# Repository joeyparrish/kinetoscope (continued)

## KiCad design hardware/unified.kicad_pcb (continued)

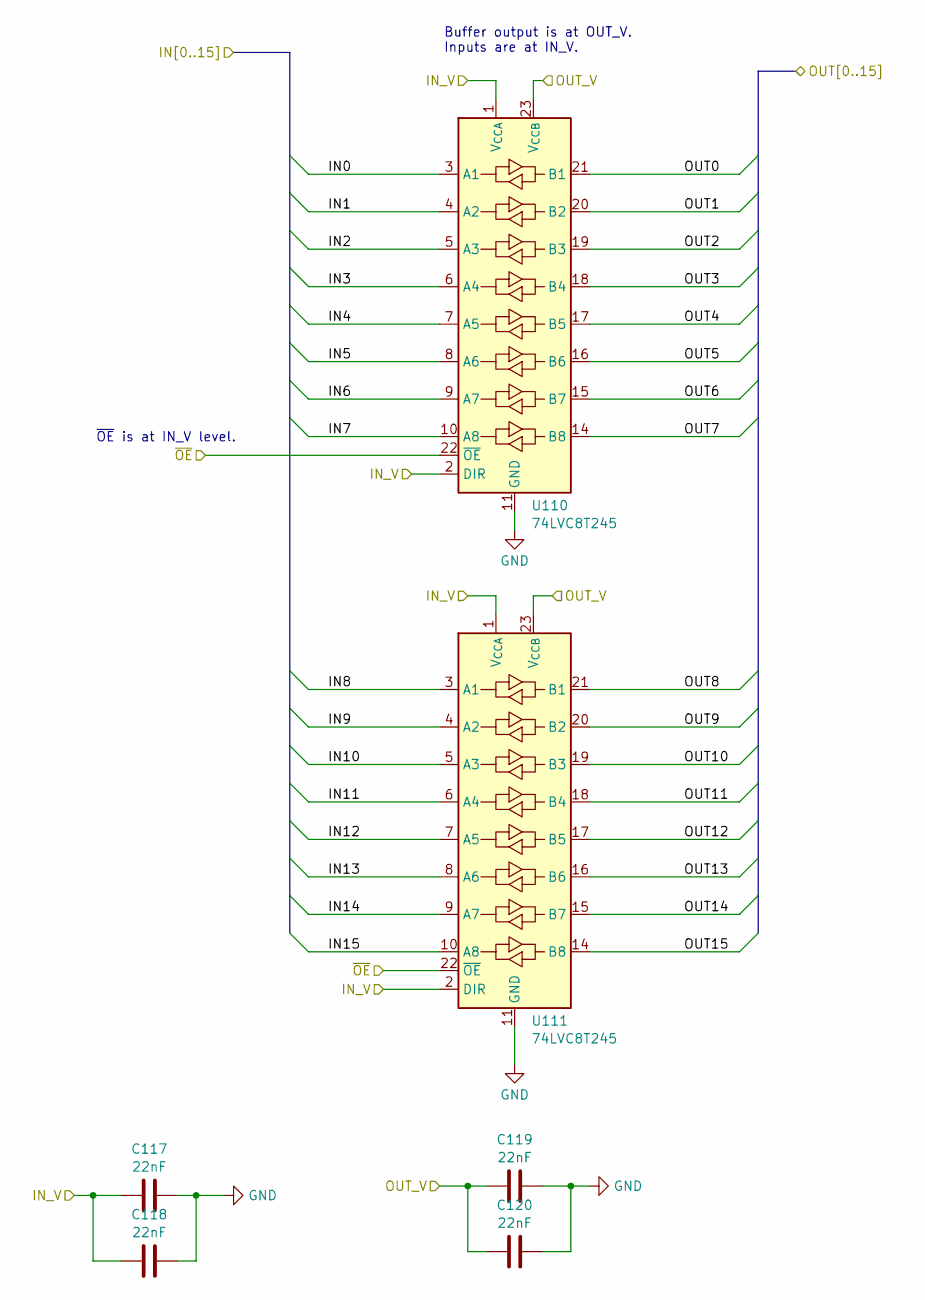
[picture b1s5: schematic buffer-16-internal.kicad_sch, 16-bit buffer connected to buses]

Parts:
C117, C118, C119, C120: 22nF; C_0603_1608Metric; Mouser Part Number 80-C0603C223K4R; JLCPCB Part Number CL10B223KB8NNNC
U110, U111: 74LVC8T245; TSSOP-24_4.4x7.8mm_P0.65mm; Mouser Part Number 595-SN74LVC8T245PWR; JLCPCB Part Number C27643

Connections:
+3.3V: C117.1, C118.1, C119.1, C120.1, U110.1 (V_{CCA}), U110.2 (DIR), U110.23 (V_{CCB}), U110.24 (V_{CCB}), U111.1 (V_{CCA}), U111.2 (DIR), U111.23 (V_{CCB}), U111.24 (V_{CCB}); also elsewhere on the board
/sram-bank-internal/SRAM_DATA0: U110.21 (B1); also elsewhere on the board
/sram-bank-internal/SRAM_DATA1: U110.20 (B2); also elsewhere on the board
/sram-bank-internal/SRAM_DATA2: U110.19 (B3); also elsewhere on the board
/sram-bank-internal/SRAM_DATA3: U110.18 (B4); also elsewhere on the board
/sram-bank-internal/SRAM_DATA4: U110.17 (B5); also elsewhere on the board
/sram-bank-internal/SRAM_DATA5: U110.16 (B6); also elsewhere on the board
/sram-bank-internal/SRAM_DATA6: U110.15 (B7); also elsewhere on the board
/sram-bank-internal/SRAM_DATA7: U110.14 (B8); also elsewhere on the board
/sram-bank-internal/SRAM_DATA8: U111.21 (B1); also elsewhere on the board
/sram-bank-internal/SRAM_DATA9: U111.20 (B2); also elsewhere on the board
/sram-bank-internal/SRAM_DATA10: U111.19 (B3); also elsewhere on the board
/sram-bank-internal/SRAM_DATA11: U111.18 (B4); also elsewhere on the board
/sram-bank-internal/SRAM_DATA12: U111.17 (B5); also elsewhere on the board
/sram-bank-internal/SRAM_DATA13: U111.16 (B6); also elsewhere on the board
/sram-bank-internal/SRAM_DATA14: U111.15 (B7); also elsewhere on the board
/sram-bank-internal/SRAM_DATA15: U111.14 (B8); also elsewhere on the board
/sram-bank-internal/~UC_CONTROL: U110.22 (~OE), U111.22 (~OE); also elsewhere on the board
GND: C117.2, C118.2, C119.2, C120.2, U110.11 (GND), U110.12 (GND), U110.13 (GND), U111.11 (GND), U111.12 (GND), U111.13 (GND); also elsewhere on the board
SRAM_D_IN0: U110.3 (A1); also elsewhere on the board
SRAM_D_IN1: U110.4 (A2); also elsewhere on the board
SRAM_D_IN2: U110.5 (A3); also elsewhere on the board
SRAM_D_IN3: U110.6 (A4); also elsewhere on the board
SRAM_D_IN4: U110.7 (A5); also elsewhere on the board
SRAM_D_IN5: U110.8 (A6); also elsewhere on the board
SRAM_D_IN6: U110.9 (A7); also elsewhere on the board
SRAM_D_IN7: U110.10 (A8); also elsewhere on the board
SRAM_D_IN8: U111.3 (A1); also elsewhere on the board
SRAM_D_IN9: U111.4 (A2); also elsewhere on the board
SRAM_D_IN10: U111.5 (A3); also elsewhere on the board
SRAM_D_IN11: U111.6 (A4); also elsewhere on the board
SRAM_D_IN12: U111.7 (A5); also elsewhere on the board
SRAM_D_IN13: U111.8 (A6); also elsewhere on the board
SRAM_D_IN14: U111.9 (A7); also elsewhere on the board
SRAM_D_IN15: U111.10 (A8); also elsewhere on the board

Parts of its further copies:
C121, C122, C123, C124, C204, C205, C206, C207, C208, C209, C210, C211: 22nF; C_0603_1608Metric; Mouser Part Number 80-C0603C223K4R; JLCPCB Part Number CL10B223KB8NNNC
U112, U113, U203, U204, U205, U206: 74LVC8T245; TSSOP-24_4.4x7.8mm_P0.65mm; Mouser Part Number 595-SN74LVC8T245PWR; JLCPCB Part Number C27643

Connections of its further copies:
+3.3V: C121.1, C122.1, C204.1, C205.1, C208.1, C209.1, C210.1, C211.1, U112.1 (V_{CCA}), U112.2 (DIR), U113.1 (V_{CCA}), U113.2 (DIR), U203.1 (V_{CCA}), U203.2 (DIR), U204.1 (V_{CCA}), U204.2 (DIR), U205.1 (V_{CCA}), U205.2 (DIR), U205.23 (V_{CCB}), U205.24 (V_{CCB}), U206.1 (V_{CCA}), U206.2 (DIR), U206.23 (V_{CCB}), U206.24 (V_{CCB}); also elsewhere on the board
+5V: C123.1, C124.1, C206.1, C207.1, U112.23 (V_{CCB}), U112.24 (V_{CCB}), U113.23 (V_{CCB}), U113.24 (V_{CCB}), U203.23 (V_{CCB}), U203.24 (V_{CCB}), U204.23 (V_{CCB}), U204.24 (V_{CCB}); also elsewhere on the board
/sram-bank-internal1/SRAM_DATA0: U203.3 (A1), U205.21 (B1); also elsewhere on the board
/sram-bank-internal1/SRAM_DATA1: U203.4 (A2), U205.20 (B2); also elsewhere on the board
/sram-bank-internal1/SRAM_DATA2: U203.5 (A3), U205.19 (B3); also elsewhere on the board
/sram-bank-internal1/SRAM_DATA3: U203.6 (A4), U205.18 (B4); also elsewhere on the board
/sram-bank-internal1/SRAM_DATA4: U203.7 (A5), U205.17 (B5); also elsewhere on the board
/sram-bank-internal1/SRAM_DATA5: U203.8 (A6), U205.16 (B6); also elsewhere on the board
/sram-bank-internal1/SRAM_DATA6: U203.9 (A7), U205.15 (B7); also elsewhere on the board
/sram-bank-internal1/SRAM_DATA7: U203.10 (A8), U205.14 (B8); also elsewhere on the board
/sram-bank-internal1/SRAM_DATA8: U204.3 (A1), U206.21 (B1); also elsewhere on the board
/sram-bank-internal1/SRAM_DATA9: U204.4 (A2), U206.20 (B2); also elsewhere on the board
/sram-bank-internal1/SRAM_DATA10: U204.5 (A3), U206.19 (B3); also elsewhere on the board
/sram-bank-internal1/SRAM_DATA11: U204.6 (A4), U206.18 (B4); also elsewhere on the board
/sram-bank-internal1/SRAM_DATA12: U204.7 (A5), U206.17 (B5); also elsewhere on the board
/sram-bank-internal1/SRAM_DATA13: U204.8 (A6), U206.16 (B6); also elsewhere on the board
/sram-bank-internal1/SRAM_DATA14: U204.9 (A7), U206.15 (B7); also elsewhere on the board
/sram-bank-internal1/SRAM_DATA15: U204.10 (A8), U206.14 (B8); also elsewhere on the board
/sram-bank-internal1/~SRAM_FINAL_OE: U203.22 (~OE), U204.22 (~OE); also elsewhere on the board
/sram-bank-internal1/~UC_CONTROL: U205.22 (~OE), U206.22 (~OE); also elsewhere on the board
/sram-bank-internal/SRAM_DATA0: U112.3 (A1); also elsewhere on the board
/sram-bank-internal/SRAM_DATA1: U112.4 (A2); also elsewhere on the board
/sram-bank-internal/SRAM_DATA2: U112.5 (A3); also elsewhere on the board
/sram-bank-internal/SRAM_DATA3: U112.6 (A4); also elsewhere on the board
/sram-bank-internal/SRAM_DATA4: U112.7 (A5); also elsewhere on the board
/sram-bank-internal/SRAM_DATA5: U112.8 (A6); also elsewhere on the board
/sram-bank-internal/SRAM_DATA6: U112.9 (A7); also elsewhere on the board
/sram-bank-internal/SRAM_DATA7: U112.10 (A8); also elsewhere on the board
/sram-bank-internal/SRAM_DATA8: U113.3 (A1); also elsewhere on the board
/sram-bank-internal/SRAM_DATA9: U113.4 (A2); also elsewhere on the board
/sram-bank-internal/SRAM_DATA10: U113.5 (A3); also elsewhere on the board
/sram-bank-internal/SRAM_DATA11: U113.6 (A4); also elsewhere on the board
/sram-bank-internal/SRAM_DATA12: U113.7 (A5); also elsewhere on the board
/sram-bank-internal/SRAM_DATA13: U113.8 (A6); also elsewhere on the board
/sram-bank-internal/SRAM_DATA14: U113.9 (A7); also elsewhere on the board
/sram-bank-internal/SRAM_DATA15: U113.10 (A8); also elsewhere on the board
/sram-bank-internal/~SRAM_FINAL_OE: U112.22 (~OE), U113.22 (~OE); also elsewhere on the board
GND: C121.2, C122.2, C123.2, C124.2, C204.2, C205.2, C206.2, C207.2, C208.2, C209.2, C210.2, C211.2, U112.11 (GND), U112.12 (GND), U112.13 (GND), U113.11 (GND), U113.12 (GND), U113.13 (GND), U203.11 (GND), U203.12 (GND), U203.13 (GND), U204.11 (GND), U204.12 (GND), U204.13 (GND), U205.11 (GND), U205.12 (GND), U205.13 (GND), U206.11 (GND), U206.12 (GND), U206.13 (GND); also elsewhere on the board
SEGA_D0: U112.21 (B1), U203.21 (B1); also elsewhere on the board
SEGA_D1: U112.20 (B2), U203.20 (B2); also elsewhere on the board
SEGA_D2: U112.19 (B3), U203.19 (B3); also elsewhere on the board
SEGA_D3: U112.18 (B4), U203.18 (B4); also elsewhere on the board
SEGA_D4: U112.17 (B5), U203.17 (B5); also elsewhere on the board
SEGA_D5: U112.16 (B6), U203.16 (B6); also elsewhere on the board
SEGA_D6: U112.15 (B7), U203.15 (B7); also elsewhere on the board
SEGA_D7: U112.14 (B8), U203.14 (B8); also elsewhere on the board
SEGA_D8: U113.21 (B1), U204.21 (B1); also elsewhere on the board
SEGA_D9: U113.20 (B2), U204.20 (B2); also elsewhere on the board
SEGA_D10: U113.19 (B3), U204.19 (B3); also elsewhere on the board
SEGA_D11: U113.18 (B4), U204.18 (B4); also elsewhere on the board
SEGA_D12: U113.17 (B5), U204.17 (B5); also elsewhere on the board
SEGA_D13: U113.16 (B6), U204.16 (B6); also elsewhere on the board
SEGA_D14: U113.15 (B7), U204.15 (B7); also elsewhere on the board
SEGA_D15: U113.14 (B8), U204.14 (B8); also elsewhere on the board
SRAM_D_IN0: U205.3 (A1); also elsewhere on the board
SRAM_D_IN1: U205.4 (A2); also elsewhere on the board
SRAM_D_IN2: U205.5 (A3); also elsewhere on the board
SRAM_D_IN3: U205.6 (A4); also elsewhere on the board
SRAM_D_IN4: U205.7 (A5); also elsewhere on the board
SRAM_D_IN5: U205.8 (A6); also elsewhere on the board
SRAM_D_IN6: U205.9 (A7); also elsewhere on the board
SRAM_D_IN7: U205.10 (A8); also elsewhere on the board
SRAM_D_IN8: U206.3 (A1); also elsewhere on the board
SRAM_D_IN9: U206.4 (A2); also elsewhere on the board
SRAM_D_IN10: U206.5 (A3); also elsewhere on the board
SRAM_D_IN11: U206.6 (A4); also elsewhere on the board
SRAM_D_IN12: U206.7 (A5); also elsewhere on the board
SRAM_D_IN13: U206.8 (A6); also elsewhere on the board
SRAM_D_IN14: U206.9 (A7); also elsewhere on the board
SRAM_D_IN15: U206.10 (A8); also elsewhere on the board

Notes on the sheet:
Buffer output is at OUT_V. Inputs are at IN_V.
~{OE} is at IN_V level.

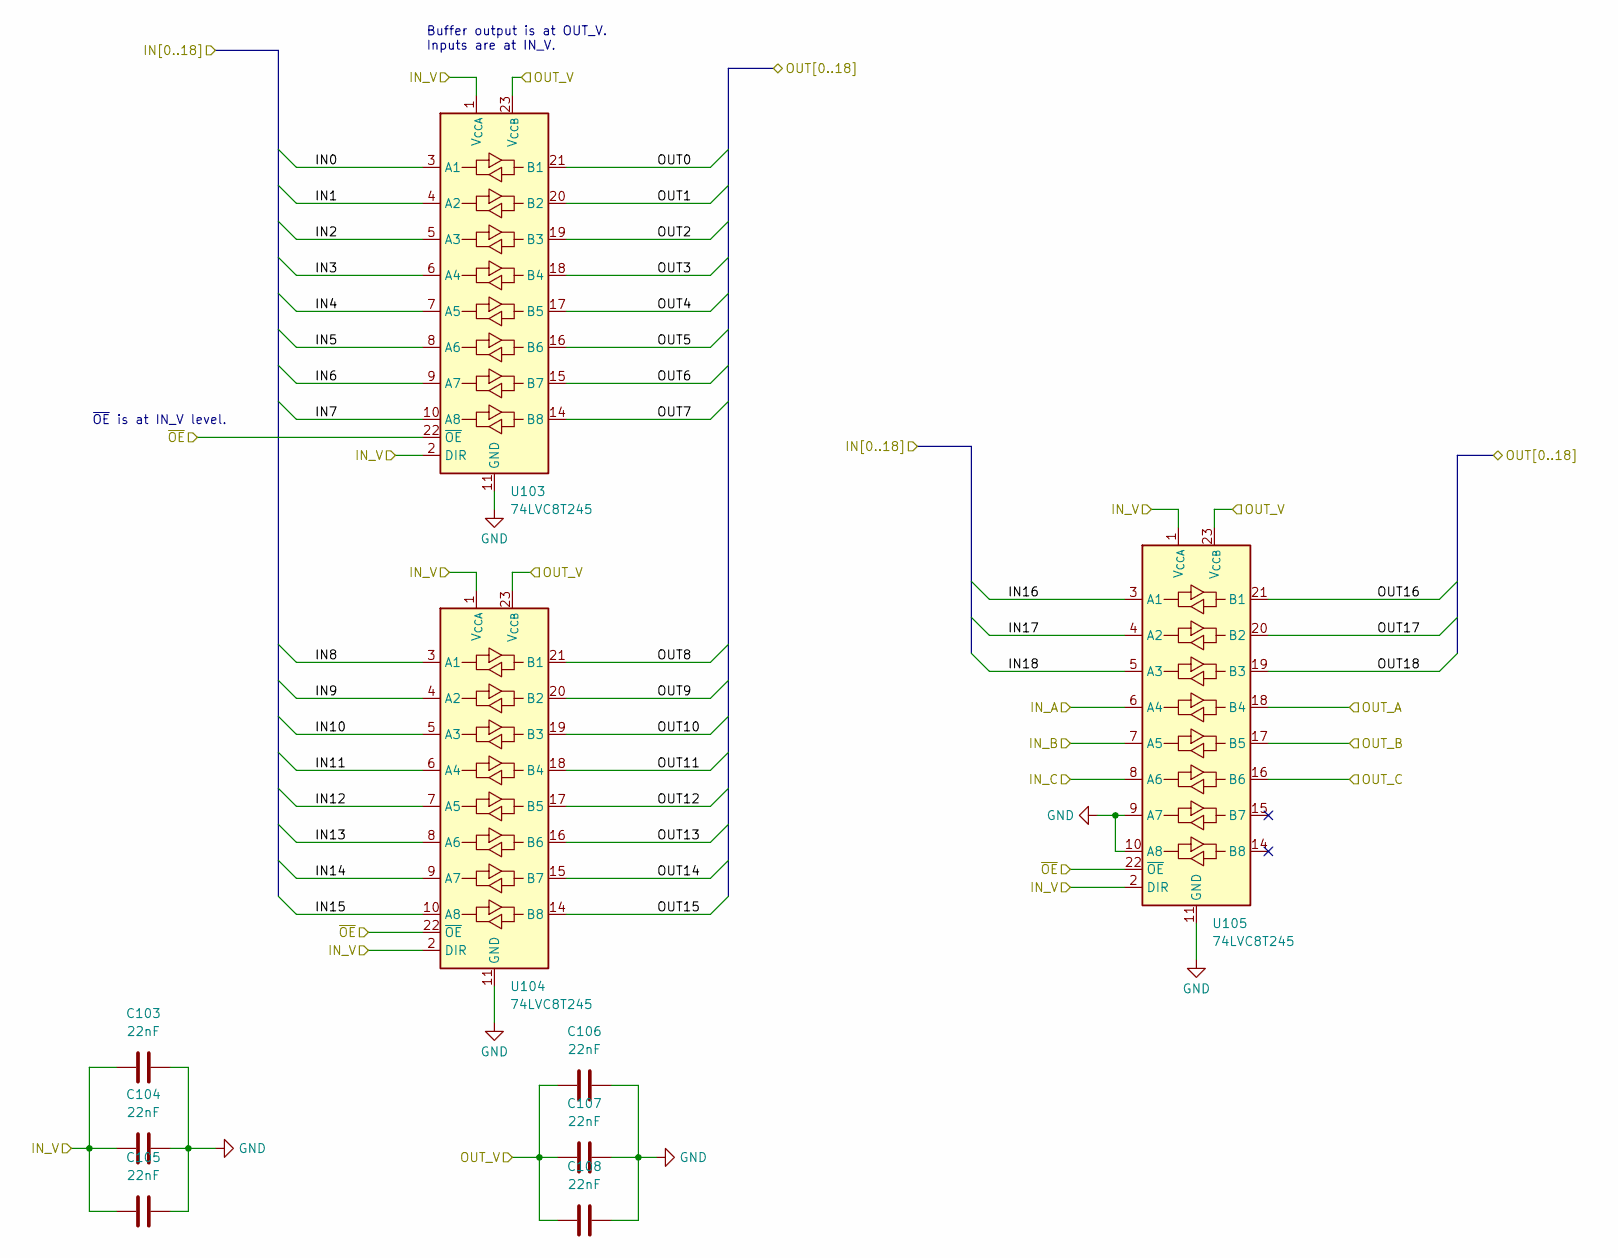
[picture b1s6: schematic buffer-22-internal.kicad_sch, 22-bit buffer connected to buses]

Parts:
C103, C104, C105, C106, C107, C108: 22nF; C_0603_1608Metric; Mouser Part Number 80-C0603C223K4R; JLCPCB Part Number CL10B223KB8NNNC
U103, U104, U105: 74LVC8T245; TSSOP-24_4.4x7.8mm_P0.65mm; Mouser Part Number 595-SN74LVC8T245PWR; JLCPCB Part Number C27643

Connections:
+3.3V: C103.1, C104.1, C105.1, C106.1, C107.1, C108.1, U103.1 (V_{CCA}), U103.2 (DIR), U103.23 (V_{CCB}), U103.24 (V_{CCB}), U104.1 (V_{CCA}), U104.2 (DIR), U104.23 (V_{CCB}), U104.24 (V_{CCB}), U105.1 (V_{CCA}), U105.2 (DIR), U105.8 (A6), U105.23 (V_{CCB}), U105.24 (V_{CCB}); also elsewhere on the board
/sram-bank-internal/SRAM_A0: U103.21 (B1); also elsewhere on the board
/sram-bank-internal/SRAM_A1: U103.20 (B2); also elsewhere on the board
/sram-bank-internal/SRAM_A2: U103.19 (B3); also elsewhere on the board
/sram-bank-internal/SRAM_A3: U103.18 (B4); also elsewhere on the board
/sram-bank-internal/SRAM_A4: U103.17 (B5); also elsewhere on the board
/sram-bank-internal/SRAM_A5: U103.16 (B6); also elsewhere on the board
/sram-bank-internal/SRAM_A6: U103.15 (B7); also elsewhere on the board
/sram-bank-internal/SRAM_A7: U103.14 (B8); also elsewhere on the board
/sram-bank-internal/SRAM_A8: U104.21 (B1); also elsewhere on the board
/sram-bank-internal/SRAM_A9: U104.20 (B2); also elsewhere on the board
/sram-bank-internal/SRAM_A10: U104.19 (B3); also elsewhere on the board
/sram-bank-internal/SRAM_A11: U104.18 (B4); also elsewhere on the board
/sram-bank-internal/SRAM_A12: U104.17 (B5); also elsewhere on the board
/sram-bank-internal/SRAM_A13: U104.16 (B6); also elsewhere on the board
/sram-bank-internal/SRAM_A14: U104.15 (B7); also elsewhere on the board
/sram-bank-internal/SRAM_A15: U104.14 (B8); also elsewhere on the board
/sram-bank-internal/SRAM_A16: U105.21 (B1); also elsewhere on the board
/sram-bank-internal/SRAM_A17: U105.20 (B2); also elsewhere on the board
/sram-bank-internal/SRAM_A18: U105.19 (B3); also elsewhere on the board
/sram-bank-internal/~SEGA_CONTROL: U103.22 (~OE), U104.22 (~OE), U105.22 (~OE); also elsewhere on the board
/sram-bank-internal/~SRAM_FINAL_CE: U105.17 (B5); also elsewhere on the board
/sram-bank-internal/~SRAM_FINAL_OE: U105.18 (B4); also elsewhere on the board
/sram-bank-internal/~SRAM_FINAL_WE: U105.16 (B6); also elsewhere on the board
/sram-bank-internal/~SRAM_OE: U105.6 (A4); also elsewhere on the board
GND: C103.2, C104.2, C105.2, C106.2, C107.2, C108.2, U103.11 (GND), U103.12 (GND), U103.13 (GND), U104.11 (GND), U104.12 (GND), U104.13 (GND), U105.9 (A7), U105.10 (A8), U105.11 (GND), U105.12 (GND), U105.13 (GND); also elsewhere on the board
SEGA_A1: U103.3 (A1); also elsewhere on the board
SEGA_A2: U103.4 (A2); also elsewhere on the board
SEGA_A3: U103.5 (A3); also elsewhere on the board
SEGA_A4: U103.6 (A4); also elsewhere on the board
SEGA_A5: U103.7 (A5); also elsewhere on the board
SEGA_A6: U103.8 (A6); also elsewhere on the board
SEGA_A7: U103.9 (A7); also elsewhere on the board
SEGA_A8: U103.10 (A8); also elsewhere on the board
SEGA_A9: U104.3 (A1); also elsewhere on the board
SEGA_A10: U104.4 (A2); also elsewhere on the board
SEGA_A11: U104.5 (A3); also elsewhere on the board
SEGA_A12: U104.6 (A4); also elsewhere on the board
SEGA_A13: U104.7 (A5); also elsewhere on the board
SEGA_A14: U104.8 (A6); also elsewhere on the board
SEGA_A15: U104.9 (A7); also elsewhere on the board
SEGA_A16: U104.10 (A8); also elsewhere on the board
SEGA_A17: U105.3 (A1); also elsewhere on the board
SEGA_A18: U105.4 (A2); also elsewhere on the board
SEGA_A19: U105.5 (A3); also elsewhere on the board
~SEGA_CE: U105.7 (A5); also elsewhere on the board

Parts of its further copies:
C109, C110, C111, C112, C113, C114, C212, C213, C214, C215, C216, C217, C218, C219, C220, C221, C222, C223: 22nF; C_0603_1608Metric; Mouser Part Number 80-C0603C223K4R; JLCPCB Part Number CL10B223KB8NNNC
U106, U107, U108, U207, U208, U209, U210, U211, U212: 74LVC8T245; TSSOP-24_4.4x7.8mm_P0.65mm; Mouser Part Number 595-SN74LVC8T245PWR; JLCPCB Part Number C27643

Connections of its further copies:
+3.3V: C109.1, C110.1, C111.1, C112.1, C113.1, C114.1, C212.1, C213.1, C214.1, C215.1, C216.1, C217.1, C218.1, C219.1, C220.1, C221.1, C222.1, C223.1, U106.1 (V_{CCA}), U106.2 (DIR), U106.23 (V_{CCB}), U106.24 (V_{CCB}), U107.1 (V_{CCA}), U107.2 (DIR), U107.23 (V_{CCB}), U107.24 (V_{CCB}), U108.1 (V_{CCA}), U108.2 (DIR), U108.6 (A4), U108.23 (V_{CCB}), U108.24 (V_{CCB}), U207.1 (V_{CCA}), U207.2 (DIR), U207.23 (V_{CCB}), U207.24 (V_{CCB}), U208.1 (V_{CCA}), U208.2 (DIR), U208.23 (V_{CCB}), U208.24 (V_{CCB}), U209.1 (V_{CCA}), U209.2 (DIR), U209.8 (A6), U209.23 (V_{CCB}), U209.24 (V_{CCB}), U210.1 (V_{CCA}), U210.2 (DIR), U210.23 (V_{CCB}), U210.24 (V_{CCB}), U211.1 (V_{CCA}), U211.2 (DIR), U211.23 (V_{CCB}), U211.24 (V_{CCB}), U212.1 (V_{CCA}), U212.2 (DIR), U212.6 (A4), U212.23 (V_{CCB}), U212.24 (V_{CCB}); also elsewhere on the board
/sram-bank-internal1/SRAM_A0: U207.21 (B1), U210.21 (B1); also elsewhere on the board
/sram-bank-internal1/SRAM_A1: U207.20 (B2), U210.20 (B2); also elsewhere on the board
/sram-bank-internal1/SRAM_A2: U207.19 (B3), U210.19 (B3); also elsewhere on the board
/sram-bank-internal1/SRAM_A3: U207.18 (B4), U210.18 (B4); also elsewhere on the board
/sram-bank-internal1/SRAM_A4: U207.17 (B5), U210.17 (B5); also elsewhere on the board
/sram-bank-internal1/SRAM_A5: U207.16 (B6), U210.16 (B6); also elsewhere on the board
/sram-bank-internal1/SRAM_A6: U207.15 (B7), U210.15 (B7); also elsewhere on the board
/sram-bank-internal1/SRAM_A7: U207.14 (B8), U210.14 (B8); also elsewhere on the board
/sram-bank-internal1/SRAM_A8: U208.21 (B1), U211.21 (B1); also elsewhere on the board
/sram-bank-internal1/SRAM_A9: U208.20 (B2), U211.20 (B2); also elsewhere on the board
/sram-bank-internal1/SRAM_A10: U208.19 (B3), U211.19 (B3); also elsewhere on the board
/sram-bank-internal1/SRAM_A11: U208.18 (B4), U211.18 (B4); also elsewhere on the board
/sram-bank-internal1/SRAM_A12: U208.17 (B5), U211.17 (B5); also elsewhere on the board
/sram-bank-internal1/SRAM_A13: U208.16 (B6), U211.16 (B6); also elsewhere on the board
/sram-bank-internal1/SRAM_A14: U208.15 (B7), U211.15 (B7); also elsewhere on the board
/sram-bank-internal1/SRAM_A15: U208.14 (B8), U211.14 (B8); also elsewhere on the board
/sram-bank-internal1/SRAM_A16: U209.21 (B1), U212.21 (B1); also elsewhere on the board
/sram-bank-internal1/SRAM_A17: U209.20 (B2), U212.20 (B2); also elsewhere on the board
/sram-bank-internal1/SRAM_A18: U209.19 (B3), U212.19 (B3); also elsewhere on the board
/sram-bank-internal1/~SEGA_CONTROL: U207.22 (~OE), U208.22 (~OE), U209.22 (~OE); also elsewhere on the board
/sram-bank-internal1/~SRAM_FINAL_CE: U209.17 (B5), U212.17 (B5); also elsewhere on the board
/sram-bank-internal1/~SRAM_FINAL_OE: U209.18 (B4), U212.18 (B4); also elsewhere on the board
/sram-bank-internal1/~SRAM_FINAL_WE: U209.16 (B6), U212.16 (B6); also elsewhere on the board
/sram-bank-internal1/~SRAM_OE: U209.6 (A4); also elsewhere on the board
/sram-bank-internal1/~UC_CONTROL: U210.22 (~OE), U211.22 (~OE), U212.22 (~OE); also elsewhere on the board
/sram-bank-internal/SRAM_A0: U106.21 (B1); also elsewhere on the board
/sram-bank-internal/SRAM_A1: U106.20 (B2); also elsewhere on the board
/sram-bank-internal/SRAM_A2: U106.19 (B3); also elsewhere on the board
/sram-bank-internal/SRAM_A3: U106.18 (B4); also elsewhere on the board
/sram-bank-internal/SRAM_A4: U106.17 (B5); also elsewhere on the board
/sram-bank-internal/SRAM_A5: U106.16 (B6); also elsewhere on the board
/sram-bank-internal/SRAM_A6: U106.15 (B7); also elsewhere on the board
/sram-bank-internal/SRAM_A7: U106.14 (B8); also elsewhere on the board
/sram-bank-internal/SRAM_A8: U107.21 (B1); also elsewhere on the board
/sram-bank-internal/SRAM_A9: U107.20 (B2); also elsewhere on the board
/sram-bank-internal/SRAM_A10: U107.19 (B3); also elsewhere on the board
/sram-bank-internal/SRAM_A11: U107.18 (B4); also elsewhere on the board
/sram-bank-internal/SRAM_A12: U107.17 (B5); also elsewhere on the board
/sram-bank-internal/SRAM_A13: U107.16 (B6); also elsewhere on the board
/sram-bank-internal/SRAM_A14: U107.15 (B7); also elsewhere on the board
/sram-bank-internal/SRAM_A15: U107.14 (B8); also elsewhere on the board
/sram-bank-internal/SRAM_A16: U108.21 (B1); also elsewhere on the board
/sram-bank-internal/SRAM_A17: U108.20 (B2); also elsewhere on the board
/sram-bank-internal/SRAM_A18: U108.19 (B3); also elsewhere on the board
/sram-bank-internal/~SRAM_FINAL_CE: U108.17 (B5); also elsewhere on the board
/sram-bank-internal/~SRAM_FINAL_OE: U108.18 (B4); also elsewhere on the board
/sram-bank-internal/~SRAM_FINAL_WE: U108.16 (B6); also elsewhere on the board
/sram-bank-internal/~UC_CONTROL: U106.22 (~OE), U107.22 (~OE), U108.22 (~OE); also elsewhere on the board
GND: C109.2, C110.2, C111.2, C112.2, C113.2, C114.2, C212.2, C213.2, C214.2, C215.2, C216.2, C217.2, C218.2, C219.2, C220.2, C221.2, C222.2, C223.2, U106.11 (GND), U106.12 (GND), U106.13 (GND), U107.11 (GND), U107.12 (GND), U107.13 (GND), U108.9 (A7), U108.10 (A8), U108.11 (GND), U108.12 (GND), U108.13 (GND), U207.11 (GND), U207.12 (GND), U207.13 (GND), U208.11 (GND), U208.12 (GND), U208.13 (GND), U209.9 (A7), U209.10 (A8), U209.11 (GND), U209.12 (GND), U209.13 (GND), U210.11 (GND), U210.12 (GND), U210.13 (GND), U211.11 (GND), U211.12 (GND), U211.13 (GND), U212.9 (A7), U212.10 (A8), U212.11 (GND), U212.12 (GND), U212.13 (GND); also elsewhere on the board
SEGA_A1: U207.3 (A1); also elsewhere on the board
SEGA_A2: U207.4 (A2); also elsewhere on the board
SEGA_A3: U207.5 (A3); also elsewhere on the board
SEGA_A4: U207.6 (A4); also elsewhere on the board
SEGA_A5: U207.7 (A5); also elsewhere on the board
SEGA_A6: U207.8 (A6); also elsewhere on the board
SEGA_A7: U207.9 (A7); also elsewhere on the board
SEGA_A8: U207.10 (A8); also elsewhere on the board
SEGA_A9: U208.3 (A1); also elsewhere on the board
SEGA_A10: U208.4 (A2); also elsewhere on the board
SEGA_A11: U208.5 (A3); also elsewhere on the board
SEGA_A12: U208.6 (A4); also elsewhere on the board
SEGA_A13: U208.7 (A5); also elsewhere on the board
SEGA_A14: U208.8 (A6); also elsewhere on the board
SEGA_A15: U208.9 (A7); also elsewhere on the board
SEGA_A16: U208.10 (A8); also elsewhere on the board
SEGA_A17: U209.3 (A1); also elsewhere on the board
SEGA_A18: U209.4 (A2); also elsewhere on the board
SEGA_A19: U209.5 (A3); also elsewhere on the board
SRAM_W_A0: U106.3 (A1), U210.3 (A1); also elsewhere on the board
SRAM_W_A1: U106.4 (A2), U210.4 (A2); also elsewhere on the board
SRAM_W_A2: U106.5 (A3), U210.5 (A3); also elsewhere on the board
SRAM_W_A3: U106.6 (A4), U210.6 (A4); also elsewhere on the board
SRAM_W_A4: U106.7 (A5), U210.7 (A5); also elsewhere on the board
SRAM_W_A5: U106.8 (A6), U210.8 (A6); also elsewhere on the board
SRAM_W_A6: U106.9 (A7), U210.9 (A7); also elsewhere on the board
SRAM_W_A7: U106.10 (A8), U210.10 (A8); also elsewhere on the board
SRAM_W_A8: U107.3 (A1), U211.3 (A1); also elsewhere on the board
SRAM_W_A9: U107.4 (A2), U211.4 (A2); also elsewhere on the board
SRAM_W_A10: U107.5 (A3), U211.5 (A3); also elsewhere on the board
SRAM_W_A11: U107.6 (A4), U211.6 (A4); also elsewhere on the board
SRAM_W_A12: U107.7 (A5), U211.7 (A5); also elsewhere on the board
SRAM_W_A13: U107.8 (A6), U211.8 (A6); also elsewhere on the board
SRAM_W_A14: U107.9 (A7), U211.9 (A7); also elsewhere on the board
SRAM_W_A15: U107.10 (A8), U211.10 (A8); also elsewhere on the board
SRAM_W_A16: U108.3 (A1), U212.3 (A1); also elsewhere on the board
SRAM_W_A17: U108.4 (A2), U212.4 (A2); also elsewhere on the board
SRAM_W_A18: U108.5 (A3), U212.5 (A3); also elsewhere on the board
~SEGA_CE: U209.7 (A5); also elsewhere on the board
~SRAM_WE: U108.7 (A5), U108.8 (A6), U212.7 (A5), U212.8 (A6); also elsewhere on the board

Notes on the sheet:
~{OE} is at IN_V level.
Buffer output is at OUT_V. Inputs are at IN_V.

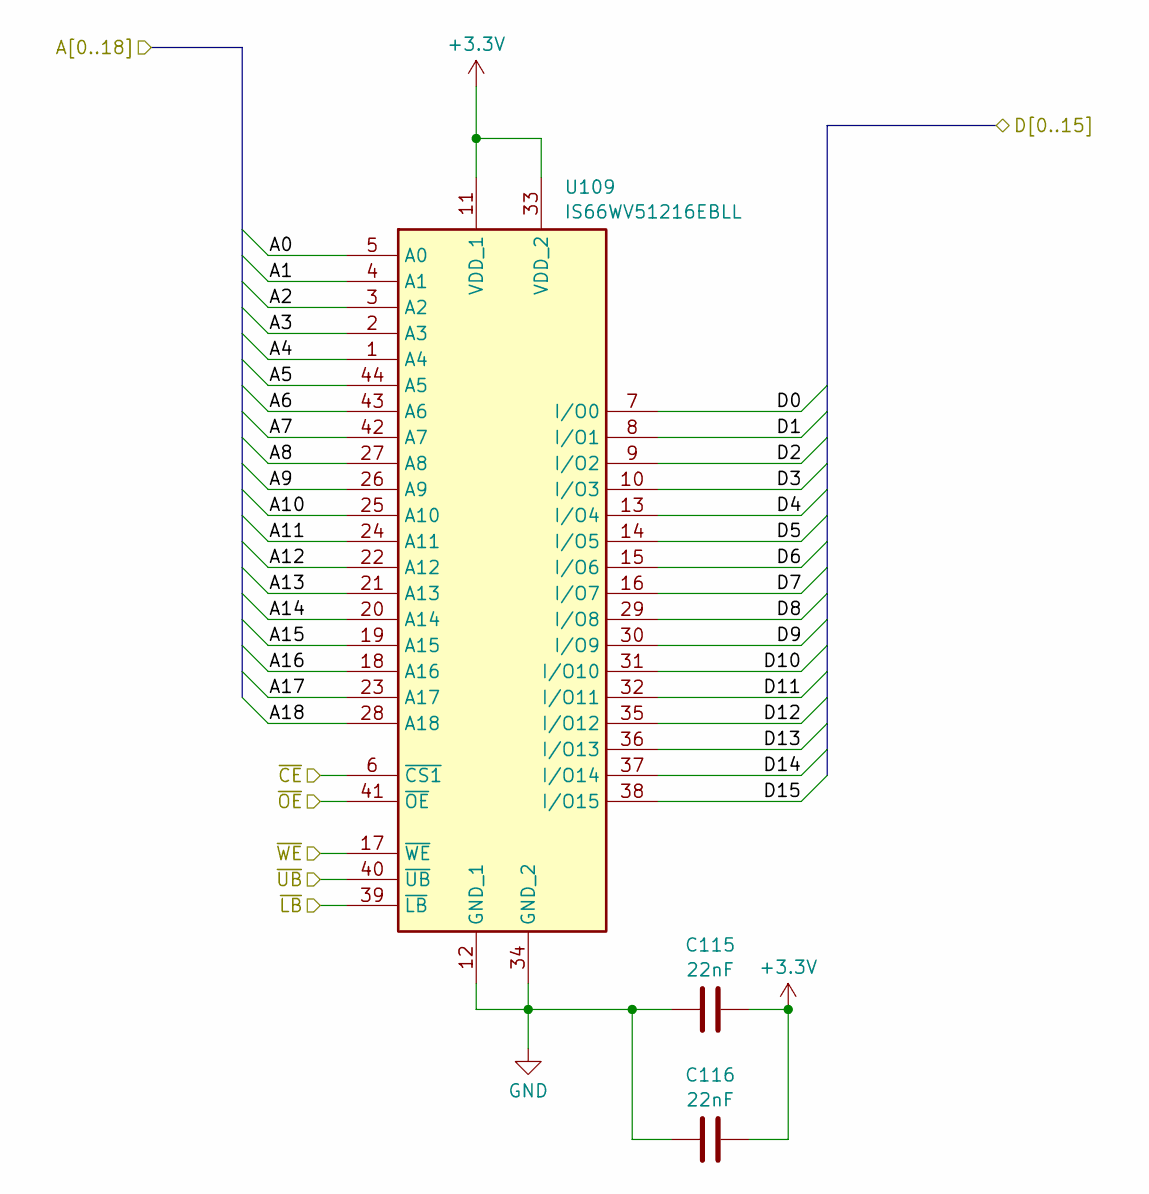
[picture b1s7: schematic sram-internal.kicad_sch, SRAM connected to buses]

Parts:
C115, C116: 22nF; C_0603_1608Metric; Mouser Part Number 80-C0603C223K4R; JLCPCB Part Number CL10B223KB8NNNC
U109: IS66WV51216EBLL; TSOP-II-44_10.16x18.41mm_P0.8mm; Mouser Part Number 870-66WV512EBLL55TLI

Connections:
+3.3V: C115.2, C116.2, U109.11 (VDD_1), U109.33 (VDD_2); also elsewhere on the board
/sram-bank-internal/SRAM_A0: U109.5 (A0); also elsewhere on the board
/sram-bank-internal/SRAM_A1: U109.4 (A1); also elsewhere on the board
/sram-bank-internal/SRAM_A2: U109.3 (A2); also elsewhere on the board
/sram-bank-internal/SRAM_A3: U109.2 (A3); also elsewhere on the board
/sram-bank-internal/SRAM_A4: U109.1 (A4); also elsewhere on the board
/sram-bank-internal/SRAM_A5: U109.44 (A5); also elsewhere on the board
/sram-bank-internal/SRAM_A6: U109.43 (A6); also elsewhere on the board
/sram-bank-internal/SRAM_A7: U109.42 (A7); also elsewhere on the board
/sram-bank-internal/SRAM_A8: U109.27 (A8); also elsewhere on the board
/sram-bank-internal/SRAM_A9: U109.26 (A9); also elsewhere on the board
/sram-bank-internal/SRAM_A10: U109.25 (A10); also elsewhere on the board
/sram-bank-internal/SRAM_A11: U109.24 (A11); also elsewhere on the board
/sram-bank-internal/SRAM_A12: U109.22 (A12); also elsewhere on the board
/sram-bank-internal/SRAM_A13: U109.21 (A13); also elsewhere on the board
/sram-bank-internal/SRAM_A14: U109.20 (A14); also elsewhere on the board
/sram-bank-internal/SRAM_A15: U109.19 (A15); also elsewhere on the board
/sram-bank-internal/SRAM_A16: U109.18 (A16); also elsewhere on the board
/sram-bank-internal/SRAM_A17: U109.23 (A17); also elsewhere on the board
/sram-bank-internal/SRAM_A18: U109.28 (A18); also elsewhere on the board
/sram-bank-internal/SRAM_DATA0: U109.7 (I/O0); also elsewhere on the board
/sram-bank-internal/SRAM_DATA1: U109.8 (I/O1); also elsewhere on the board
/sram-bank-internal/SRAM_DATA2: U109.9 (I/O2); also elsewhere on the board
/sram-bank-internal/SRAM_DATA3: U109.10 (I/O3); also elsewhere on the board
/sram-bank-internal/SRAM_DATA4: U109.13 (I/O4); also elsewhere on the board
/sram-bank-internal/SRAM_DATA5: U109.14 (I/O5); also elsewhere on the board
/sram-bank-internal/SRAM_DATA6: U109.15 (I/O6); also elsewhere on the board
/sram-bank-internal/SRAM_DATA7: U109.16 (I/O7); also elsewhere on the board
/sram-bank-internal/SRAM_DATA8: U109.29 (I/O8); also elsewhere on the board
/sram-bank-internal/SRAM_DATA9: U109.30 (I/O9); also elsewhere on the board
/sram-bank-internal/SRAM_DATA10: U109.31 (I/O10); also elsewhere on the board
/sram-bank-internal/SRAM_DATA11: U109.32 (I/O11); also elsewhere on the board
/sram-bank-internal/SRAM_DATA12: U109.35 (I/O12); also elsewhere on the board
/sram-bank-internal/SRAM_DATA13: U109.36 (I/O13); also elsewhere on the board
/sram-bank-internal/SRAM_DATA14: U109.37 (I/O14); also elsewhere on the board
/sram-bank-internal/SRAM_DATA15: U109.38 (I/O15); also elsewhere on the board
/sram-bank-internal/~SRAM_FINAL_CE: U109.6 (~CS1); also elsewhere on the board
/sram-bank-internal/~SRAM_FINAL_OE: U109.41 (~OE); also elsewhere on the board
/sram-bank-internal/~SRAM_FINAL_WE: U109.17 (~WE); also elsewhere on the board
GND: C115.1, C116.1, U109.12 (GND_1), U109.34 (GND_2), U109.39 (~LB), U109.40 (~UB); also elsewhere on the board

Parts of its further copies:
C202, C203: 22nF; C_0603_1608Metric; Mouser Part Number 80-C0603C223K4R; JLCPCB Part Number CL10B223KB8NNNC
U202: IS66WV51216EBLL; TSOP-II-44_10.16x18.41mm_P0.8mm; Mouser Part Number 870-66WV512EBLL55TLI

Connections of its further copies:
+3.3V: C202.2, C203.2, U202.11 (VDD_1), U202.33 (VDD_2); also elsewhere on the board
/sram-bank-internal1/SRAM_A0: U202.5 (A0); also elsewhere on the board
/sram-bank-internal1/SRAM_A1: U202.4 (A1); also elsewhere on the board
/sram-bank-internal1/SRAM_A2: U202.3 (A2); also elsewhere on the board
/sram-bank-internal1/SRAM_A3: U202.2 (A3); also elsewhere on the board
/sram-bank-internal1/SRAM_A4: U202.1 (A4); also elsewhere on the board
/sram-bank-internal1/SRAM_A5: U202.44 (A5); also elsewhere on the board
/sram-bank-internal1/SRAM_A6: U202.43 (A6); also elsewhere on the board
/sram-bank-internal1/SRAM_A7: U202.42 (A7); also elsewhere on the board
/sram-bank-internal1/SRAM_A8: U202.27 (A8); also elsewhere on the board
/sram-bank-internal1/SRAM_A9: U202.26 (A9); also elsewhere on the board
/sram-bank-internal1/SRAM_A10: U202.25 (A10); also elsewhere on the board
/sram-bank-internal1/SRAM_A11: U202.24 (A11); also elsewhere on the board
/sram-bank-internal1/SRAM_A12: U202.22 (A12); also elsewhere on the board
/sram-bank-internal1/SRAM_A13: U202.21 (A13); also elsewhere on the board
/sram-bank-internal1/SRAM_A14: U202.20 (A14); also elsewhere on the board
/sram-bank-internal1/SRAM_A15: U202.19 (A15); also elsewhere on the board
/sram-bank-internal1/SRAM_A16: U202.18 (A16); also elsewhere on the board
/sram-bank-internal1/SRAM_A17: U202.23 (A17); also elsewhere on the board
/sram-bank-internal1/SRAM_A18: U202.28 (A18); also elsewhere on the board
/sram-bank-internal1/SRAM_DATA0: U202.7 (I/O0); also elsewhere on the board
/sram-bank-internal1/SRAM_DATA1: U202.8 (I/O1); also elsewhere on the board
/sram-bank-internal1/SRAM_DATA2: U202.9 (I/O2); also elsewhere on the board
/sram-bank-internal1/SRAM_DATA3: U202.10 (I/O3); also elsewhere on the board
/sram-bank-internal1/SRAM_DATA4: U202.13 (I/O4); also elsewhere on the board
/sram-bank-internal1/SRAM_DATA5: U202.14 (I/O5); also elsewhere on the board
/sram-bank-internal1/SRAM_DATA6: U202.15 (I/O6); also elsewhere on the board
/sram-bank-internal1/SRAM_DATA7: U202.16 (I/O7); also elsewhere on the board
/sram-bank-internal1/SRAM_DATA8: U202.29 (I/O8); also elsewhere on the board
/sram-bank-internal1/SRAM_DATA9: U202.30 (I/O9); also elsewhere on the board
/sram-bank-internal1/SRAM_DATA10: U202.31 (I/O10); also elsewhere on the board
/sram-bank-internal1/SRAM_DATA11: U202.32 (I/O11); also elsewhere on the board
/sram-bank-internal1/SRAM_DATA12: U202.35 (I/O12); also elsewhere on the board
/sram-bank-internal1/SRAM_DATA13: U202.36 (I/O13); also elsewhere on the board
/sram-bank-internal1/SRAM_DATA14: U202.37 (I/O14); also elsewhere on the board
/sram-bank-internal1/SRAM_DATA15: U202.38 (I/O15); also elsewhere on the board
/sram-bank-internal1/~SRAM_FINAL_CE: U202.6 (~CS1); also elsewhere on the board
/sram-bank-internal1/~SRAM_FINAL_OE: U202.41 (~OE); also elsewhere on the board
/sram-bank-internal1/~SRAM_FINAL_WE: U202.17 (~WE); also elsewhere on the board
GND: C202.1, C203.1, U202.12 (GND_1), U202.34 (GND_2), U202.39 (~LB), U202.40 (~UB); also elsewhere on the board
